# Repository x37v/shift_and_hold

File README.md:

# Shift + Sample and Hold

This PCB is a 4 output 1 input sample and hold, 4 output trigger interface driven by a single analog input and shift register.
The boards are meant to cascade. The goal is to drive my drum-machine triggers and accent levels.

The sample and hold is based of this project:
http://www.supersynthesis.com/pages/lf398-sample-hold

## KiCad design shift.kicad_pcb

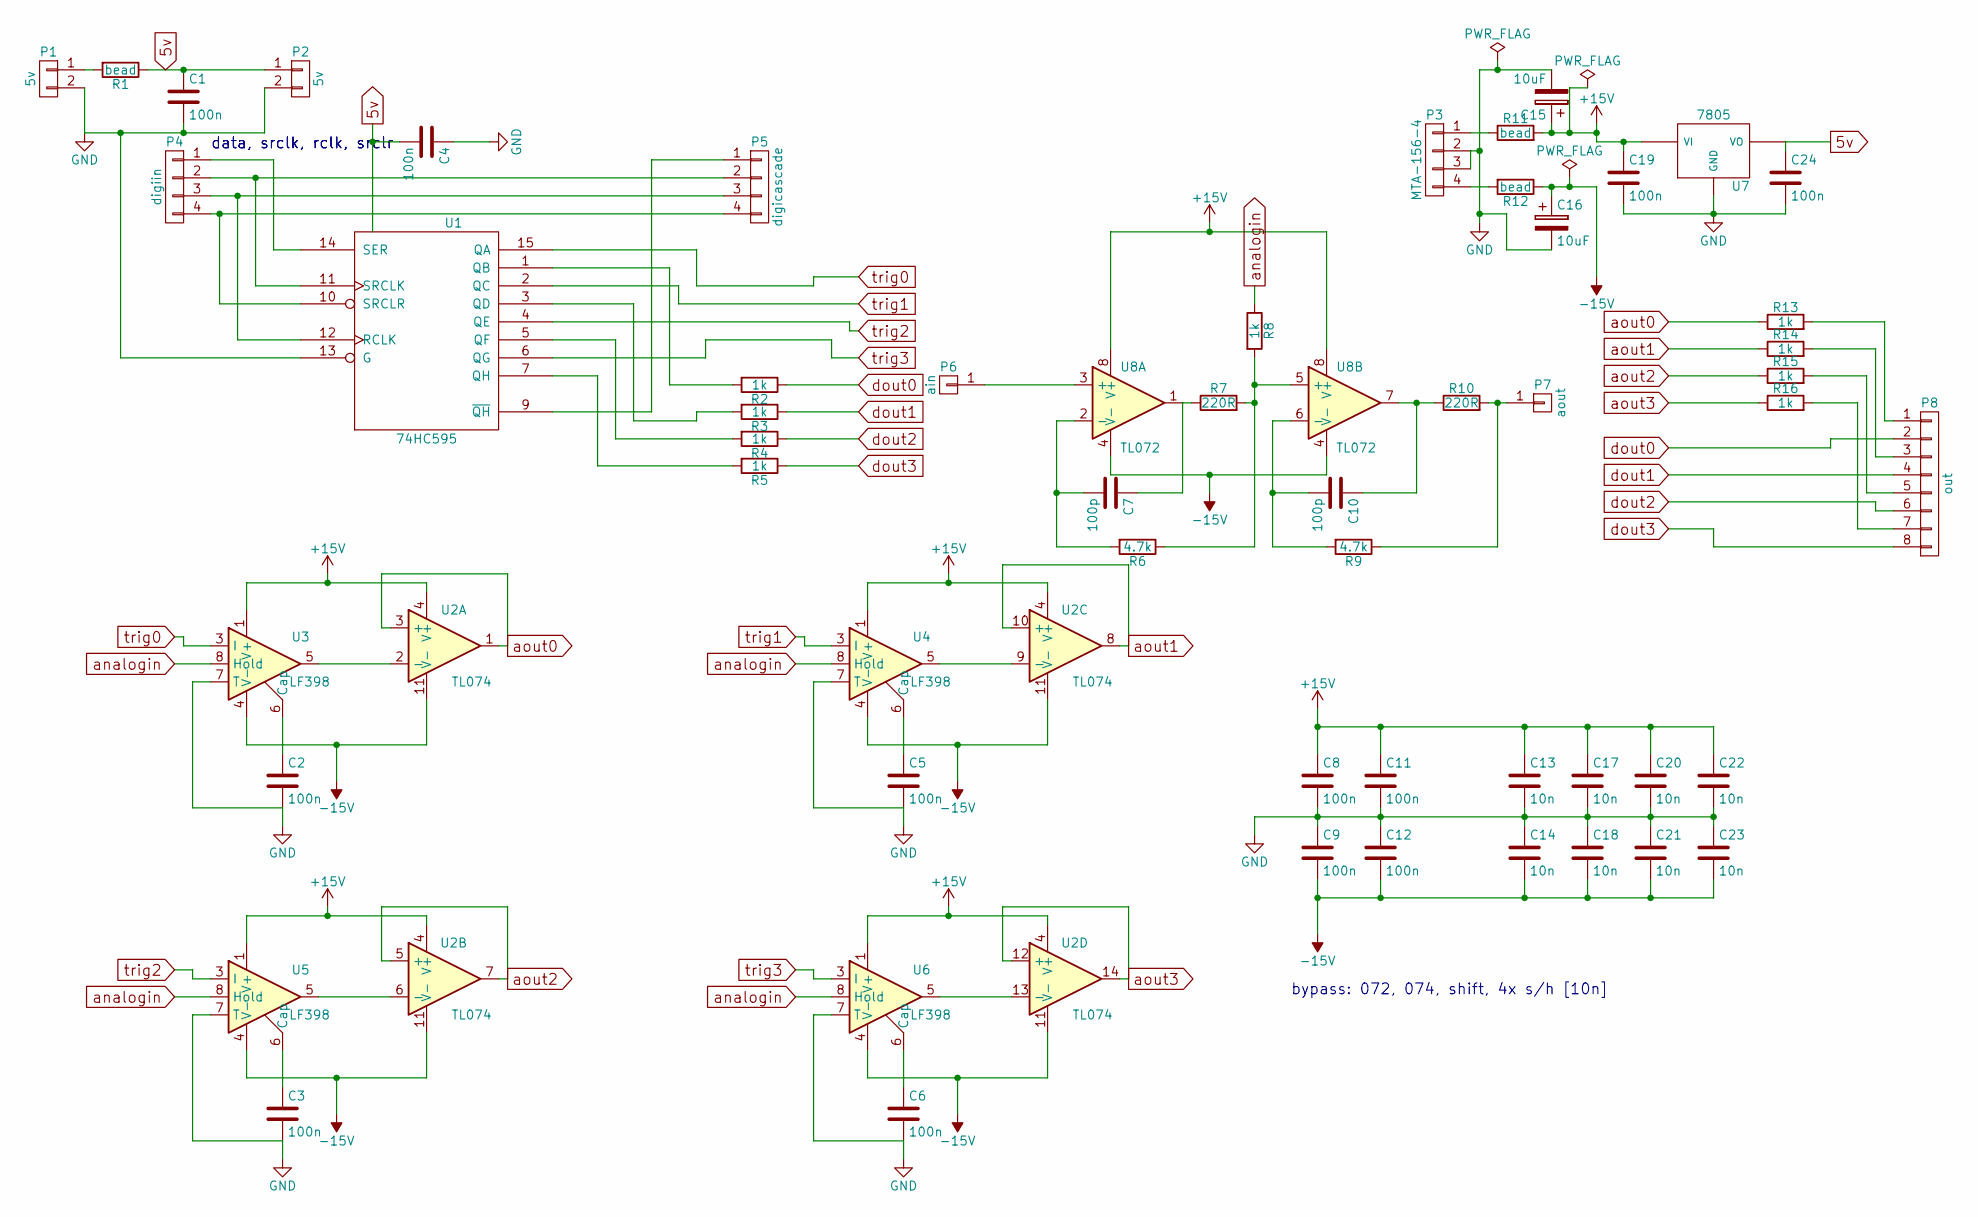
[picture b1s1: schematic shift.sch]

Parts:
C1, C4, C8, C9, C11, C12, C19, C24: 100n; C_Rect_L4_W2.5_P2.5
C2, C3, C5, C6: 100n; C_Rect_L7_W4.5_P5
C7, C10: 100p; C_Rect_L4_W2.5_P2.5
C13, C14, C17, C18, C20, C21, C22, C23: 10n; C_Rect_L4_W2.5_P2.5
C15, C16: 10uF; CP_Radial_Tantal_D7.0mm_P2.50mm
P1, P2: 5v; Pin_Header_Straight_1x02
P3: MTA-156-4
P4: digiin; Pin_Header_Straight_1x04
P5: digicascade; Pin_Header_Straight_1x04
P6: ain; Pin_Header_Straight_1x01
P7: aout; Pin_Header_Straight_1x01
P8: out; Pin_Header_Straight_1x08
R1, R11, R12: bead; Resistor_Vertical_RM5mm
R2, R3, R4, R5, R8, R13, R14, R15, R16: 1k; Resistor_Vertical_RM5mm
R6, R9: 4.7k; Resistor_Vertical_RM5mm
R7, R10: 220R; Resistor_Vertical_RM5mm
U1: 74HC595; DIP-16_W7.62mm_LongPads
U2: TL074; DIP-14_W7.62mm_Socket_LongPads
U3, U4, U5, U6: LF398; DIP-8_W7.62mm_LongPads
U7: 7805; TO-220_Vertical
U8: TL072; DIP-8_W7.62mm_LongPads

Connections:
5v: C1.1, C4.2, C24.1, P2.1, R1.1, U1.16 (VCC), U7.3 (VO)
+15V: C8.1, C11.1, C13.1, C15.1, C17.1, C19.1, C20.1, C22.1, R11.2, U2.4 (V+), U3.1 (V+), U4.1 (V+), U5.1 (V+), U6.1 (V+), U7.1 (VI), U8.8 (V+)
-15V: C9.2, C12.2, C14.2, C16.1, C18.2, C21.2, C23.2, R12.1, U2.11 (V-), U3.4 (V-), U4.4 (V-), U5.4 (V-), U6.4 (V-), U8.4 (V-)
GND: C1.2, C2.2, C3.2, C4.1, C5.2, C6.2, C8.2, C9.1, C11.2, C12.1, C13.2, C14.1, C15.2, C16.2, C17.2, C18.1, C19.2, C20.2, C21.1, C22.2, C23.1, C24.2, P1.2, P2.2, P3.2, P3.3, U1.8 (GND), U1.13 (G), U3.7 (T), U4.7 (T), U5.7 (T), U6.7 (T), U7.2 (GND)
unnamed: C2.1, U3.6 (Cap)
unnamed: C3.1, U5.6 (Cap)
unnamed: C5.1, U4.6 (Cap)
unnamed: C6.1, U6.6 (Cap)
unnamed: C7.1, R7.1, U8.1
unnamed: C7.2, R6.2, U8.2 (-)
unnamed: C10.1, R10.1, U8.7
unnamed: C10.2, R9.2, U8.6 (-)
unnamed: P1.1, R1.2
unnamed: P3.1, R11.1
unnamed: P3.4, R12.2
unnamed: P4.1, U1.14 (SER)
unnamed: P4.2, P5.2, U1.11 (SRCLK)
unnamed: P4.3, P5.3, U1.12 (RCLK)
unnamed: P4.4, P5.4, U1.10 (SRCLR)
unnamed: P5.1, U1.9 (~QH)
unnamed: P6.1, U8.3 (+)
unnamed: P7.1, R9.1, R10.2
unnamed: P8.1, R13.2
unnamed: P8.3, R14.2
unnamed: P8.5, R15.2
unnamed: P8.7, R16.2
unnamed: R2.2, U1.1 (QB)
unnamed: R3.2, U1.3 (QD)
unnamed: R4.2, U1.5 (QF)
unnamed: R5.2, U1.7 (QH)
unnamed: R6.1, R7.2, R8.2, U8.5 (+)
unnamed: U2.2 (-), U3.5
unnamed: U2.6 (-), U5.5
unnamed: U2.9 (-), U4.5
unnamed: U2.13 (-), U6.5
analogin: R8.1, U3.8 (Hold), U4.8 (Hold), U5.8 (Hold), U6.8 (Hold)
aout0: R13.1, U2.1, U2.3 (+)
aout1: R14.1, U2.8, U2.10 (+)
aout2: R15.1, U2.5 (+), U2.7
aout3: R16.1, U2.12 (+), U2.14
dout0: P8.2, R2.1
dout1: P8.4, R3.1
dout2: P8.6, R4.1
dout3: P8.8, R5.1
trig0: U1.15 (QA), U3.3 (I)
trig1: U1.2 (QC), U4.3 (I)
trig2: U1.4 (QE), U5.3 (I)
trig3: U1.6 (QG), U6.3 (I)

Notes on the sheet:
data, srclk, rclk, srclr
bypass: 072, 074, shift, 4x s/h [10n]

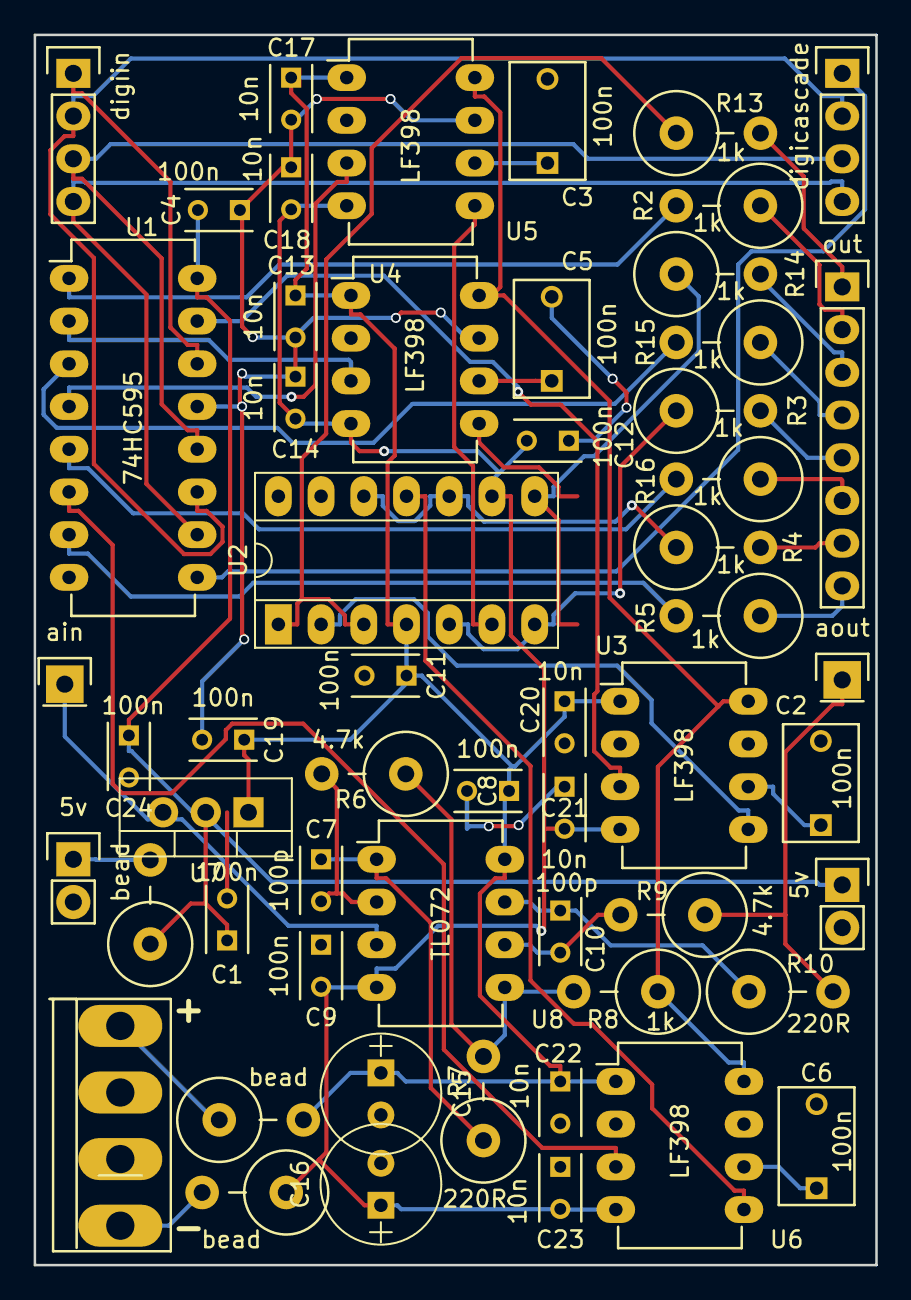
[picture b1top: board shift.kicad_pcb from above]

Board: 2 copper layers, 50.0 x 73.2 mm, 56 parts (0 on the bottom side), 48 nets.

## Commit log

2016-10-26 real basic project setup
2016-10-28 updates... added correct header
2016-10-29 decouple caps, all layed out [i think] except routing
2016-10-29 auto routed and filled
2016-10-29 ignoring auto router files
2016-10-29 everything is hooked up, moved around too
2017-01-20 added some text
2017-01-20 added readme
2017-01-20 attribution for sample and hold
2017-09-06 updated footprints for the bad 074 and vreg
2017-09-06 updated caps to be bigger and added power flags
2017-09-06 updated with new footprints, need to layout
